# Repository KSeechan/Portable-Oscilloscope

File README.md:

# Portable-Oscilloscope
Design of a Portable Oscilloscope

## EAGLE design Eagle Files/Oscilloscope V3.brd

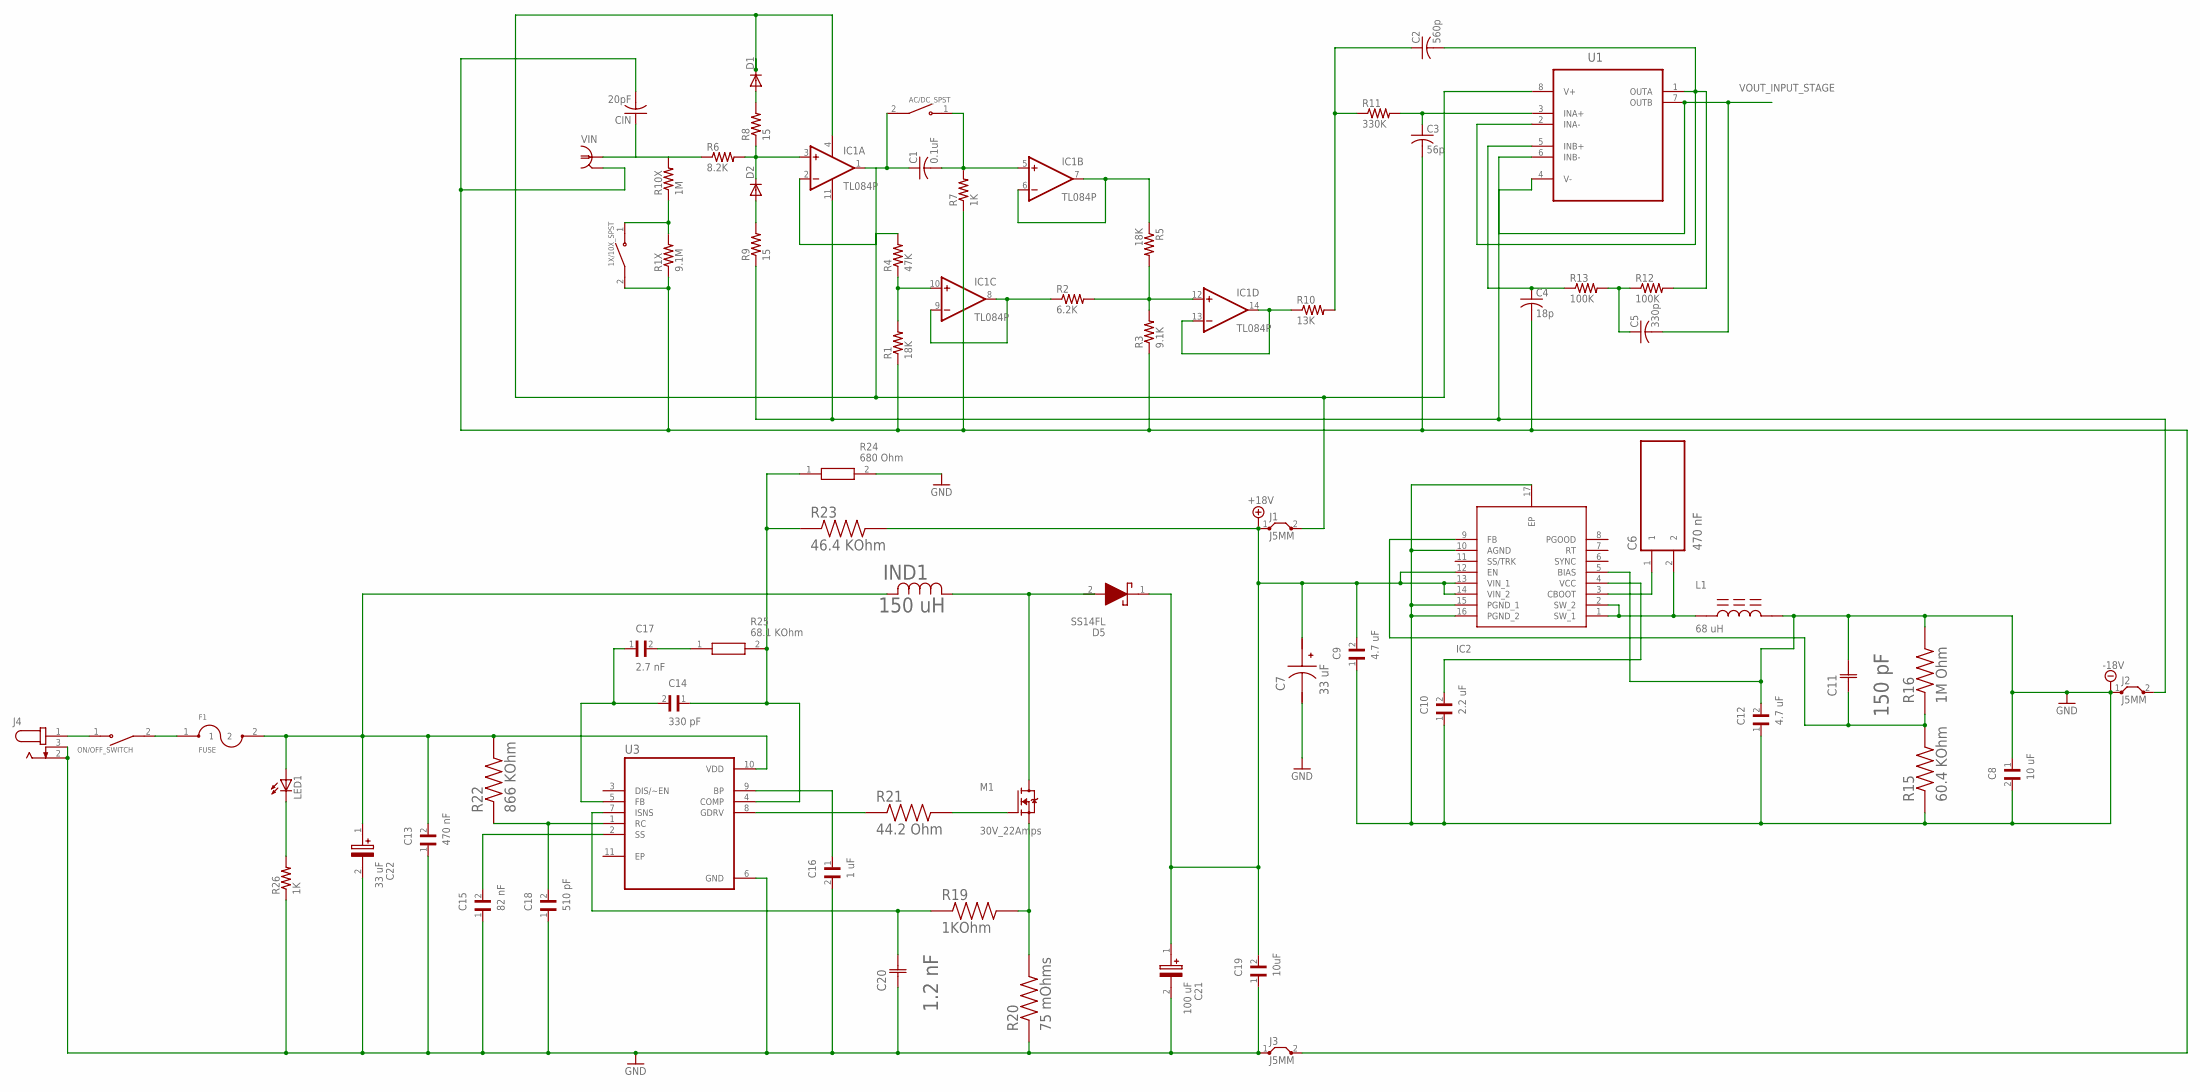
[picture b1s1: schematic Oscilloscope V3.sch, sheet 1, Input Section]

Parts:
1X/10X_SPST: GF-123-0054; SW_GF-123-0054
AC/DC_SPST: GF-123-0054; SW_GF-123-0054
C1: 0.1uF; C075-052X106
C2: 560p; C050-024X044
C3: 56p; C050-024X044
C4: 18p; C050-024X044
C5: 330p; C050-024X044
C6: 470 nF; CAPC1005X55N
C7: 33 uF; SM_RADIAL_C
C8: 10 uF; ANTC3225X280N
C9: 4.7 uF; CAPC2012X145N
C10: 2.2 uF; CAPC2012X135N
C11: 150 pF; CAPC2013X88N
C12: 4.7 uF; CAPC1608X90N
C13: 470 nF; CAPC2012X95N
C14: 330 pF; CAPC2012X140N
C15: 82 nF; CAPC1005X55N
C16: 1 uF; CAPC2012X88N
C17: 2.7 nF; CAPC2012X75N
C18: 510 pF; CAPC1005X55N
C19: 10uF; CAPC2012X140N
C20: 1.2 nF; CAPC2013X88N
C21: 100 uF; CAPAE830X1050N
C22: 33 uF; CAPAE660X610N
CIN: 20pF; C150-072X183
D1, D2: DIODE-DO204-10; DO204-10
D5: SS14FL; SODFL3617X108N
F1: FUSE; FUSM4632X75
IC1: TL084P; DIL14
IC2: LM43601PWPR; SOP65P640X120-17N
IND1: 150 uH; IND_NPI105C_NIC
J1, J2, J3: J5MM; 05
J4: PJ-202B; CUI_PJ-202B
L1: 68 uH; IND_SDR0403-680KL
LED1: LED_ELD260; LED_LD260
M1: 30V_22Amps; TRANS_CSD17571Q2
ON/OFF_SWITCH: GF-123-0054; SW_GF-123-0054
R1, R5: 18K; 0309/10
R1X: 9.1M; 0309/10
R2: 6.2K; 0309/10
R3: 9.1K; 0309/10
R4: 47K; 0309/10
R6: 8.2K; 0309/10
R7, R26: 1K; 0309/10
R8, R9: 15; 0309/10
R10: 13K; 0309/10
R10X: 1M; 0309/10
R11: 330K; 0309/10
R12, R13: 100K; 0309/10
R15: 60.4 KOhm; RESC1005X40N
R16: 1M Ohm; RESC1005X40N
R19: 1KOhm; RESC1005X40N
R20: 75 mOhms; RESC1608X55N
R21: 44.2 Ohm; RESC1005X40N
R22: 866 KOhm; RESC0603X26N
R23: 46.4 KOhm; RESC1005X40N
R24: 680 Ohm; RESC1608X55N
R25: 68.1 KOhm; RESC1608X55N
U1: ADA4062-2BRZ; SOIC127P600X175-8N
U3: TPS40211DGQR; IC_XTR111AIDGQR
VIN: 1-227161-6; AMP_227161

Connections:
+18V: C7.1 (+), C9.2, C19.2, C21.1 (+), D5.1 (K), IC2.12 (EN), IC2.13 (VIN_1), IC2.14 (VIN_2), J1.1, R23.2
-18V: C8.1, C8.2, C9.1, C10.1, C11.2 (C2), C12.1, C12.2, IC2.5 (BIAS), IC2.10 (AGND), IC2.15 (PGND_1), IC2.16 (PGND_2), IC2.17 (EP), J2.1, L1.2, R15.1, R16.2
GND: C7.2 (-), C13.1, C15.1, C16.2, C18.1, C19.1, C20.1 (C1), C21.2 (-), C22.2 (-), J3.1, J4.2, J4.3, R20.1, R24.2, R26.1, U3.6 (GND); also elsewhere on the board
unnamed: CIN.1, R6.1, R10X.2, VIN.1
unnamed: 1X/10X_SPST.1, R1X.2, R10X.1
unnamed: AC/DC_SPST.1, C1.2, IC1.5 (+IN), R7.2
unnamed: AC/DC_SPST.2, C1.1, IC1.1 (OUT)
unnamed: IC1.6 (-IN), IC1.7 (OUT), R5.1
unnamed: IC1.8 (OUT), IC1.9 (-IN), R2.1
unnamed: IC1.10 (+IN), R1.2, R4.1
unnamed: IC1.12 (+IN), R2.2, R3.2, R5.2
unnamed: D2.C, IC1.3 (+IN), R6.2, R8.1
unnamed: IC1.13 (-IN), IC1.14 (OUT), R10.1
unnamed: D2.A, R9.2
unnamed: D1.A, R8.2
unnamed: C2.1, R10.2, R11.1
unnamed: C3.1, R11.2, U1.3 (INA+)
unnamed: C5.1, R12.1, R13.2
unnamed: C2.2, R12.2, U1.1 (OUTA), U1.2 (INA-)
unnamed: C14.2, C17.1, U3.5 (FB)
unnamed: C4.1, R13.1, U1.5 (INB+)
unnamed: C14.1, R23.1, R24.1, R25.2, U3.4 (COMP)
unnamed: C17.2, R25.1
unnamed: C13.2, C22.1 (+), F1.2, IND1.2, LED1.A, R22.2, U3.10 (VDD)
unnamed: C16.1, U3.9 (BP)
unnamed: C18.2, R22.1, U3.1 (RC)
unnamed: C15.2, U3.2 (SS)
unnamed: C20.2 (C2), R19.1, U3.7 (ISNS)
unnamed: R21.1, U3.8 (GDRV)
unnamed: M1.3 (G), R21.2
unnamed: F1.1, ON/OFF_SWITCH.2
unnamed: M1.4 (S), M1.8 (S), R19.2, R20.2
unnamed: LED1.K (C), R26.2
unnamed: C10.2, IC2.4 (VCC)
unnamed: IND1.1, M1.1 (D), M1.2 (D), M1.5 (D), M1.6 (D), M1.7 (D)
unnamed: D1.C, IC1.4 (V+)
unnamed: C11.1 (C1), IC2.9 (FB), R15.2, R16.1
unnamed: C6.1, IC2.3 (CBOOT)
unnamed: J1.2, R4.2, U1.8 (V+)
unnamed: IC1.11 (V-), J2.2, R9.1, U1.4 (V-)
unnamed: C6.2, IC2.1 (SW_1), IC2.2 (SW_2), L1.1
unnamed: J4.1, ON/OFF_SWITCH.1
unnamed: 1X/10X_SPST.2, C3.2, C4.2, CIN.2, J3.2, R1.1, R1X.1, R3.1, R7.1, VIN.2
VOUT_INPUT_STAGE: C5.2, U1.6 (INB-), U1.7 (OUTB); also elsewhere on the board

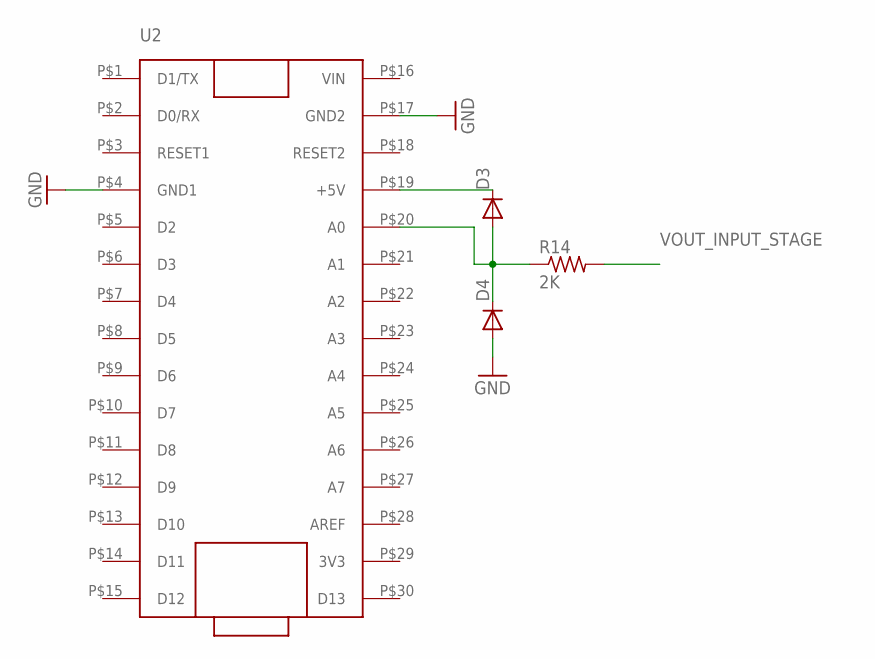
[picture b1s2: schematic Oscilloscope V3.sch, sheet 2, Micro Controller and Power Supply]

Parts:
D3, D4: DIODE-DO204-10; DO204-10
R14: 2K; 0309/10
U2: ARDUINO-NANO; NANO-PCB

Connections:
GND: D4.A, U2.P$4 (GND1), U2.P$17 (GND2); also elsewhere on the board
unnamed: D3.A, D4.C, R14.1, U2.P$20 (A0)
unnamed: D3.C, U2.P$19 (+5V)
VOUT_INPUT_STAGE: R14.2; also elsewhere on the board

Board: 2 copper layers, 72 parts (0 on the bottom side), 46 nets, no tracks yet.

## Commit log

2023-03-03 Create asd
2023-03-03 Final Report
2023-03-03 PCB Board
2023-03-03 Create as
2023-03-03 Schematic
2023-03-03 Report
2023-03-03 Board
2023-03-03 Create ger
2023-03-03 Gerber Files
2023-03-03 Create gd
2023-03-03 Pictures of Schematic and Board
2023-03-03 Create eag
2023-03-03 Eagle files for oscilloscope
2023-03-03 Create asf
2023-03-03 Necessary Library Files for Oscilloscope
2023-03-03 PCB Images
2023-03-03 Real Life Images
